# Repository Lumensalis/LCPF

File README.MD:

# Lumensalis CircuitPython Framework

This is a collection of CircuitPython code for use with TerrainTronics products sponsored by [Lumensalis Terrain](https://lumensalis.com)
 
 General project overview : https://lumensalis.com/Projects/LCPF

 - [Quick Start for the technically challenged...](docs/GettingStarted/QuickStart.mdx)
 
 - [Supported Controllers](docs/Controllers/SupportedControllers.mdx)
   - currently the ONLY tested controller is the [LolinS2Mini ESP32-S2](docs/Controllers/LolinS2Mini.mdx)
   - to setup a new LolinS2Mini, first do the [initial CircuitPython install](docs/Controllers/LolinS2Mini.mdx#initial-setup), then install the [dependencies](docs/CIRCUITPY_Dependncies.mdx)

 - [Getting Started](docs/GettingStarted/GettingStarted.mdx)
 - [Repo Contents](docs/RepoContents.mdx)

 - [source subrepo](https://github.com/Lumensalis/LCPF) 
  - most actual source code is in https://github.com/Lumensalis/LCPF
  - this repo holds most of the documentation, mechanisms for
    managing CircuitPython dependencies, and other bits related
    to the project _other_ than the framework code

# License
 
This is NOT an Open Source project.  The _only_ thing the license permits you
to use this for is your own personal projects.  You can _NOT_ share this
software _OR ANYTHING YOU BUILD USING IT_ with anyone else under
this license.

I will _probably_ change to a less restrictive license at some point, although 
it will probably _NOT_ allow any form of commercial use, especially selling 
any physical products including this software pre-installed.  I'd
prefer changing to an Open Source(ish) license, _if_ I can find one that
allows me to keep things free and easy _only_ for personal use.

If there is interest, I'll provide additional commercial license options.  

I'm also open to releasing this under a completely Open Source license in 
exchange for ongoing support of the project, although there would be a
 _substantial_ initial cost.  This may only be three months of effort so 
 far, but it's based on close to three decades of experience.

Actual license is in [License.txt](LICENSE.txt).

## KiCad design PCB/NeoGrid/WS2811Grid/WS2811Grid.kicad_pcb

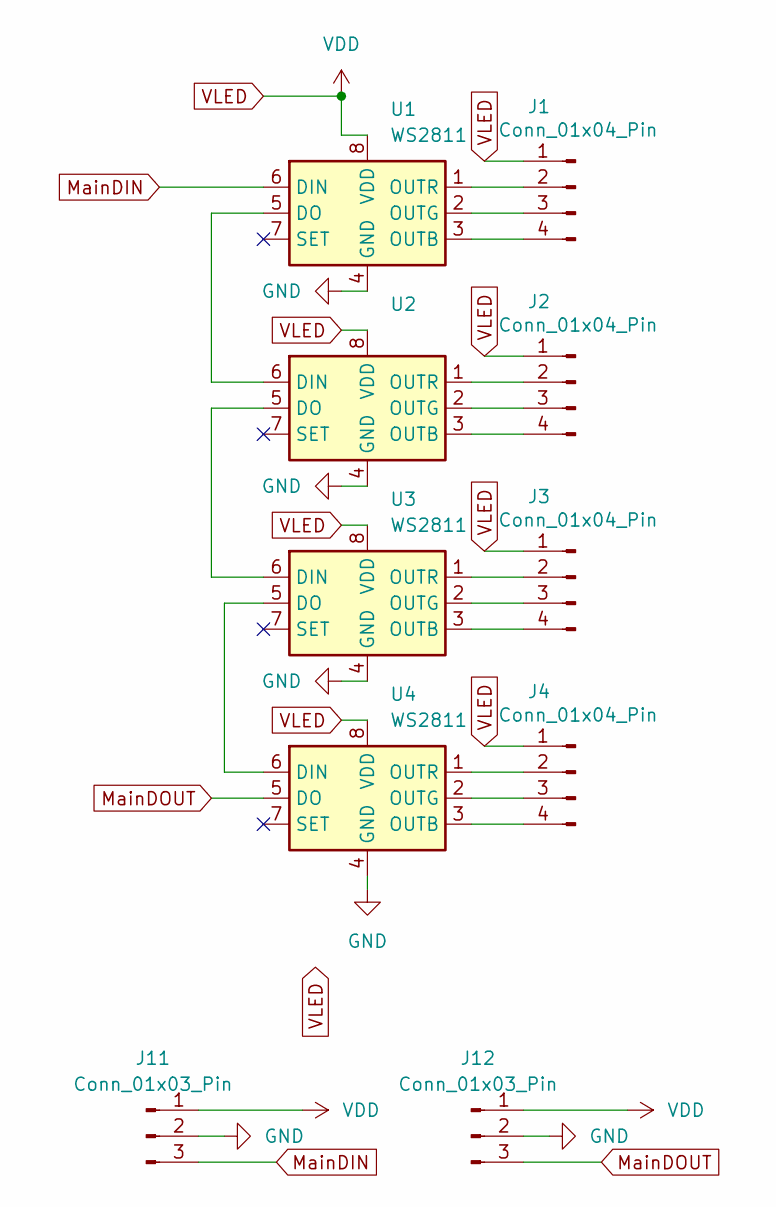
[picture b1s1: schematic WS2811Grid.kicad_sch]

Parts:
J1, J2, J3, J4: Conn_01x04_Pin; PinHeader_1x04_P2.54mm_Vertical
J11, J12: Conn_01x03_Pin; PinHeader_1x03_P2.54mm_Vertical
U1, U2, U3, U4: WS2811; SOIC-8_3.9x4.9mm_P1.27mm

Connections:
GND: J11.2, J12.2, U1.4 (GND), U2.4 (GND), U3.4 (GND), U4.4 (GND)
MainDIN: J11.3, U1.6 (DIN)
MainDOUT: J12.3, U4.5 (DO)
unnamed: J1.2, U1.1 (OUTR)
unnamed: J1.3, U1.2 (OUTG)
unnamed: J1.4, U1.3 (OUTB)
unnamed: J2.2, U2.1 (OUTR)
unnamed: J2.3, U2.2 (OUTG)
unnamed: J2.4, U2.3 (OUTB)
unnamed: J3.2, U3.1 (OUTR)
unnamed: J3.3, U3.2 (OUTG)
unnamed: J3.4, U3.3 (OUTB)
unnamed: J4.2, U4.1 (OUTR)
unnamed: J4.3, U4.2 (OUTG)
unnamed: J4.4, U4.3 (OUTB)
unnamed: U1.5 (DO), U2.6 (DIN)
unnamed: U2.5 (DO), U3.6 (DIN)
unnamed: U3.5 (DO), U4.6 (DIN)
VLED: J1.1, J2.1, J3.1, J4.1, J11.1, J12.1, U1.8 (VDD), U2.8 (VDD), U3.8 (VDD), U4.8 (VDD)

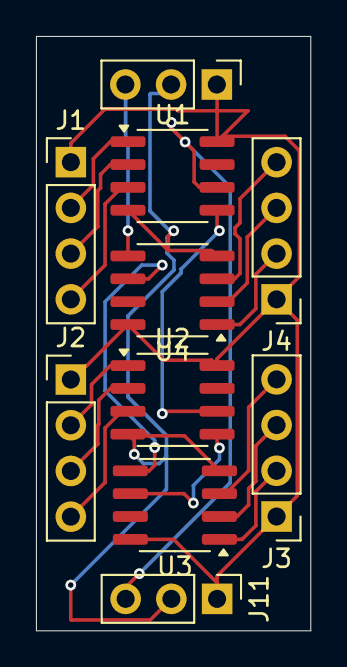
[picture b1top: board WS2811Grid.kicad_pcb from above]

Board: 2 copper layers, 15.2 x 33.0 mm, 10 parts (0 on the bottom side), 19 nets.

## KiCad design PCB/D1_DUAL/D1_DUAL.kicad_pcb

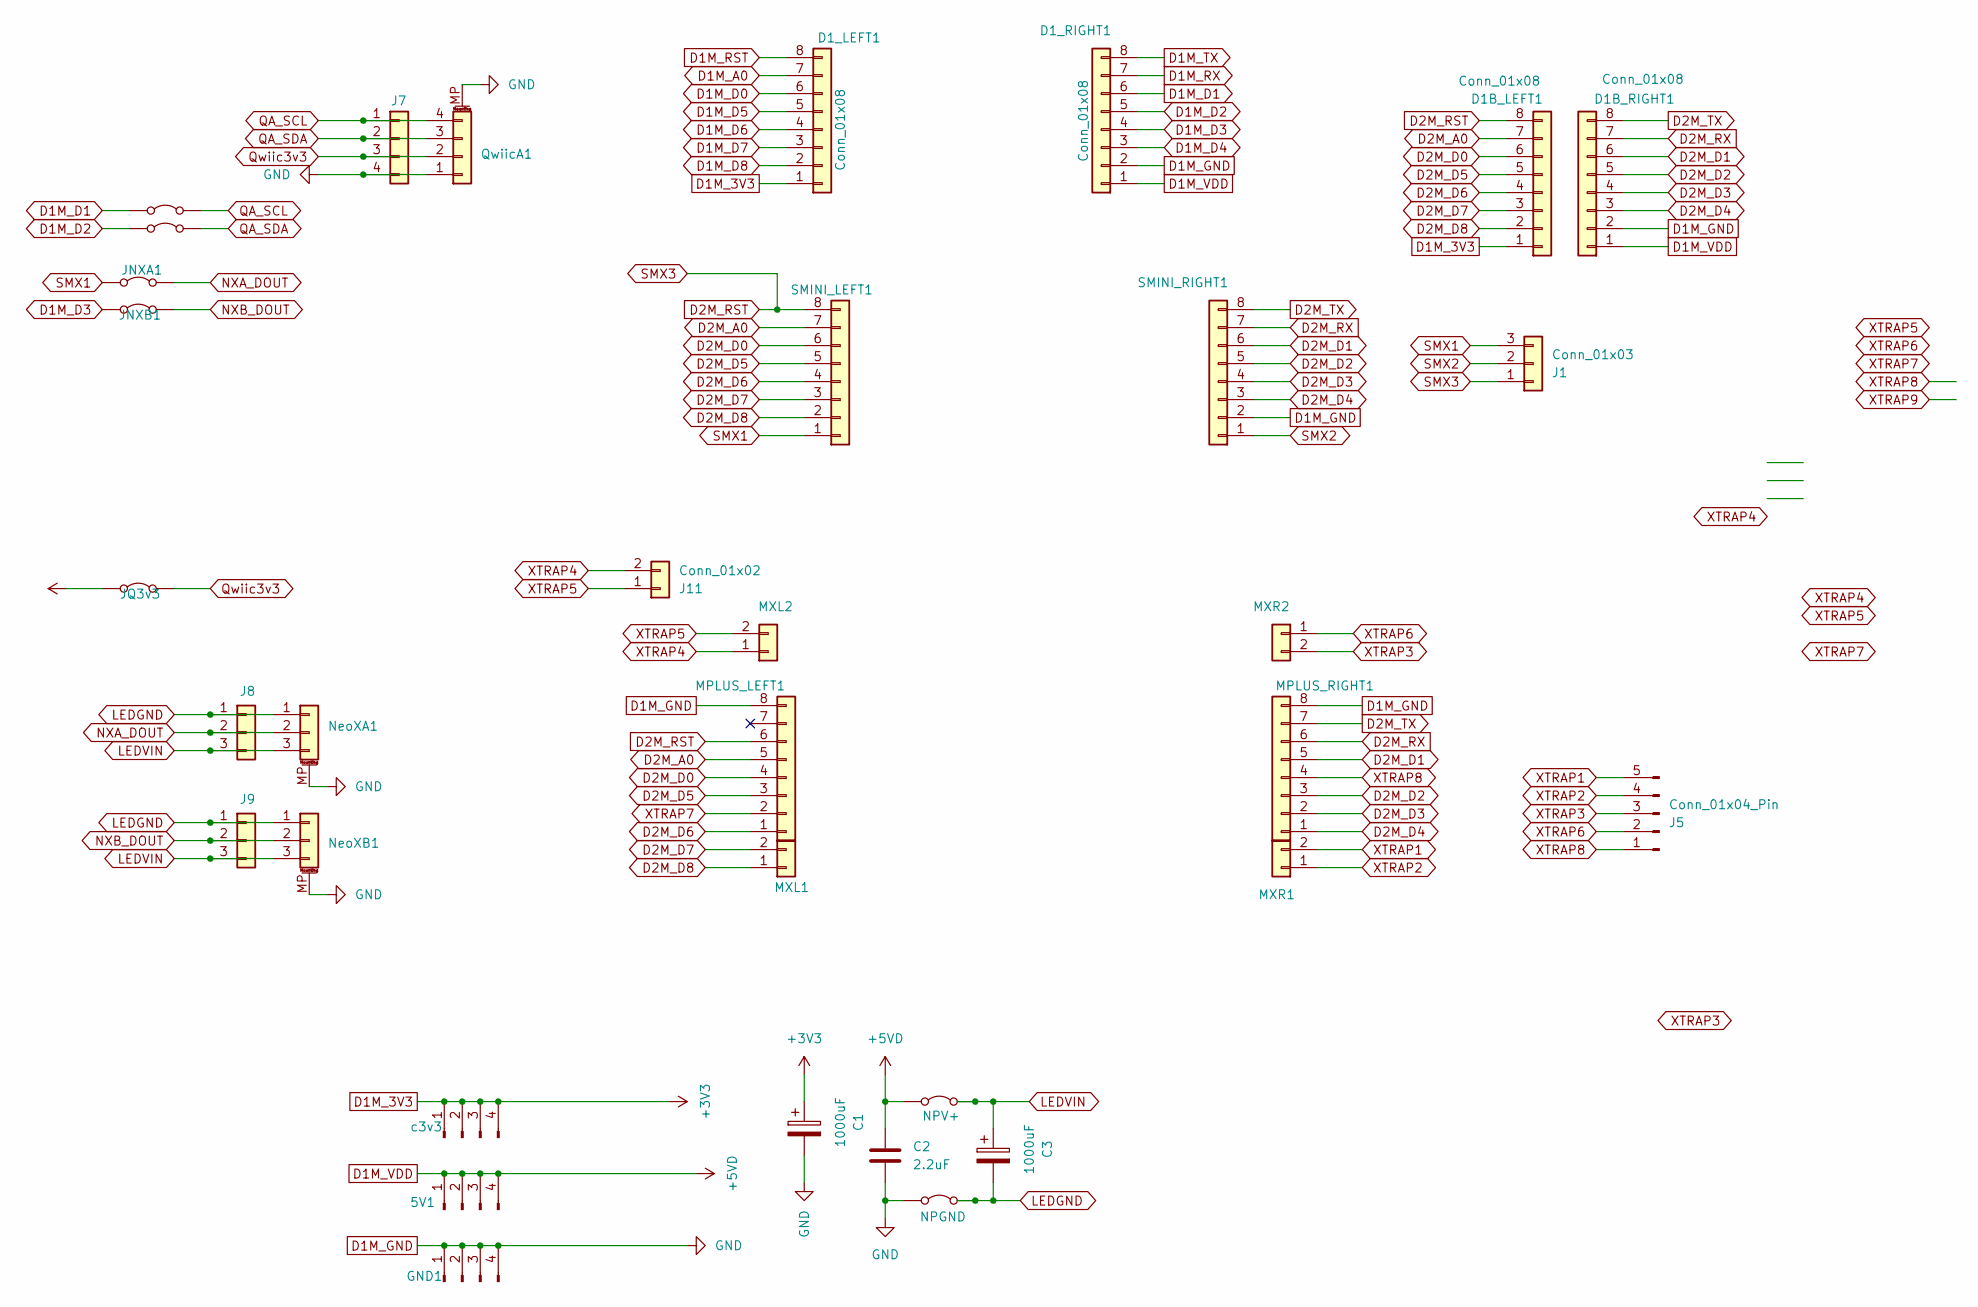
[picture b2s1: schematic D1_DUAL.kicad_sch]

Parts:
5V1: Conn_01x04_Pin; PinHeader_1x04_P2.54mm_Vertical
C1, C3: 1000uF; CP_Radial_D4.0mm_P1.50mm
C2: 2.2uF; C_Disc_D3.0mm_W2.0mm_P2.50mm
D1B_LEFT1, D1B_RIGHT1, D1_LEFT1, D1_RIGHT1: Conn_01x08; PinSocket_1x08_P2.54mm_Vertical
GND1: Conn_01x04_Pin; PinHeader_1x04_P2.54mm_Vertical
J1: Conn_01x03; PinHeader_1x03_P2.54mm_Horizontal
J5: Conn_01x04_Pin; PinHeader_1x05_P2.54mm_Horizontal
J7: Conn_01x04; PinHeader_1x04_P2.54mm_Vertical
J8, J9: Conn_01x03; PinHeader_1x03_P2.54mm_Vertical
J11: Conn_01x02; PinHeader_1x02_P2.54mm_Horizontal
JLGND1: NPGND; PinHeader_1x02_P2.54mm_Vertical
JLVDD1: NPV+; PinHeader_1x02_P2.54mm_Vertical
JNXA1: SolderJumper_2_Bridged; SolderJumper-2_P1.3mm_Bridged_RoundedPad1.0x1.5mm
JNXB1: SolderJumper_2_Bridged; SolderJumper-2_P1.3mm_Bridged_RoundedPad1.0x1.5mm
JQ3v3: SolderJumper_2_Bridged; SolderJumper-2_P1.3mm_Bridged2Bar_RoundedPad1.0x1.5mm
MPLUS_LEFT1: Conn_01x8; PinSocket_1x08_P2.54mm_Vertical
MPLUS_RIGHT1: Conn_01x8; PinSocket_1x08_P2.54mm_Vertical
MXL1, MXL2: Conn_01x02; PinSocket_1x02_P2.54mm_Vertical
MXR1, MXR2: Conn_01x02; PinSocket_1x02_P2.54mm_Vertical
NeoXA1: Conn_01x03_MountingPin; JST_GH_SM03B-GHS-TB_1x03-1MP_P1.25mm_Horizontal
NeoXB1: Conn_01x03_MountingPin; JST_GH_SM03B-GHS-TB_1x03-1MP_P1.25mm_Horizontal
QwiicA1: Conn_01x04_MountingPin; JST_SH_SM04B-SRSS-TB_1x04-1MP_P1.00mm_Horizontal
SCL_A1: SolderJumper_2_Bridged; SolderJumper-2_P1.3mm_Bridged_RoundedPad1.0x1.5mm
SDA_A1: SolderJumper_2_Bridged; SolderJumper-2_P1.3mm_Bridged_RoundedPad1.0x1.5mm
SMINI_LEFT1: Conn_01x08; PinSocket_1x08_P2.54mm_Vertical
SMINI_RIGHT1: Conn_01x08; PinSocket_1x08_P2.54mm_Vertical
c3v3: Conn_01x04_Pin; PinHeader_1x02_P2.54mm_Vertical

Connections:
D1M_3V3: C1.1, D1B_LEFT1.1, D1_LEFT1.1, JQ3v3.1 (A), c3v3.1, c3v3.2, c3v3.3, c3v3.4
D1M_A0: D1_LEFT1.7
D1M_D0: D1_LEFT1.6
D1M_D1: D1_RIGHT1.6, SCL_A1.1 (A)
D1M_D2: D1_RIGHT1.5, SDA_A1.1 (A)
D1M_D3: D1_RIGHT1.4, JNXB1.1 (A)
D1M_D4: D1_RIGHT1.3
D1M_D5: D1_LEFT1.5
D1M_D6: D1_LEFT1.4
D1M_D7: D1_LEFT1.3
D1M_D8: D1_LEFT1.2
D1M_GND: C1.2, C2.2, D1B_RIGHT1.2, D1_RIGHT1.2, GND1.1, GND1.2, GND1.3, GND1.4, J7.4, JLGND1.1 (A), MPLUS_LEFT1.8, MPLUS_RIGHT1.8, NeoXA1.MP (MountPin), NeoXB1.MP (MountPin), QwiicA1.1, QwiicA1.MP (MountPin), SMINI_RIGHT1.2
D1M_RST: D1_LEFT1.8
D1M_RX: D1_RIGHT1.7
D1M_TX: D1_RIGHT1.8
D1M_VDD: 5V1.1, 5V1.2, 5V1.3, 5V1.4, C2.1, D1B_RIGHT1.1, D1_RIGHT1.1, JLVDD1.1 (A)
D2M_A0: D1B_LEFT1.7, MPLUS_LEFT1.5, SMINI_LEFT1.7
D2M_D0: D1B_LEFT1.6, MPLUS_LEFT1.4, SMINI_LEFT1.6
D2M_D1: D1B_RIGHT1.6, MPLUS_RIGHT1.5, SMINI_RIGHT1.6
D2M_D2: D1B_RIGHT1.5, MPLUS_RIGHT1.3, SMINI_RIGHT1.5
D2M_D3: D1B_RIGHT1.4, MPLUS_RIGHT1.2, SMINI_RIGHT1.4
D2M_D4: D1B_RIGHT1.3, MPLUS_RIGHT1.1, SMINI_RIGHT1.3
D2M_D5: D1B_LEFT1.5, MPLUS_LEFT1.3, SMINI_LEFT1.5
D2M_D6: D1B_LEFT1.4, MPLUS_LEFT1.1, SMINI_LEFT1.4
D2M_D7: D1B_LEFT1.3, MXL1.2, SMINI_LEFT1.3
D2M_D8: D1B_LEFT1.2, MXL1.1, SMINI_LEFT1.2
D2M_RST: D1B_LEFT1.8, J1.1, MPLUS_LEFT1.6, SMINI_LEFT1.8
D2M_RX: D1B_RIGHT1.7, MPLUS_RIGHT1.6, SMINI_RIGHT1.7
D2M_TX: D1B_RIGHT1.8, MPLUS_RIGHT1.7, SMINI_RIGHT1.8
LEDGND: C3.2, J8.1, J9.1, JLGND1.2 (B), NeoXA1.1, NeoXB1.1
LEDVIN: C3.1, J8.3, J9.3, JLVDD1.2 (B), NeoXA1.3, NeoXB1.3
NXA_DOUT: J8.2, JNXA1.2 (B), NeoXA1.2
NXB_DOUT: J9.2, JNXB1.2 (B), NeoXB1.2
QA_SCL: J7.1, QwiicA1.4, SCL_A1.2 (B)
QA_SDA: J7.2, QwiicA1.3, SDA_A1.2 (B)
Qwiic3v3: J7.3, JQ3v3.2 (B), QwiicA1.2
SMX1: J1.3, JNXA1.1 (A), SMINI_LEFT1.1
SMX2: J1.2, SMINI_RIGHT1.1
XTRAP1: J5.5, MXR1.2
XTRAP2: J5.4, MXR1.1
XTRAP3: J5.3, MXR2.2
XTRAP4: J11.2, MXL2.1
XTRAP5: J11.1, MXL2.2
XTRAP6: J5.2, MXR2.1
XTRAP7: MPLUS_LEFT1.2
XTRAP8: J5.1, MPLUS_RIGHT1.4

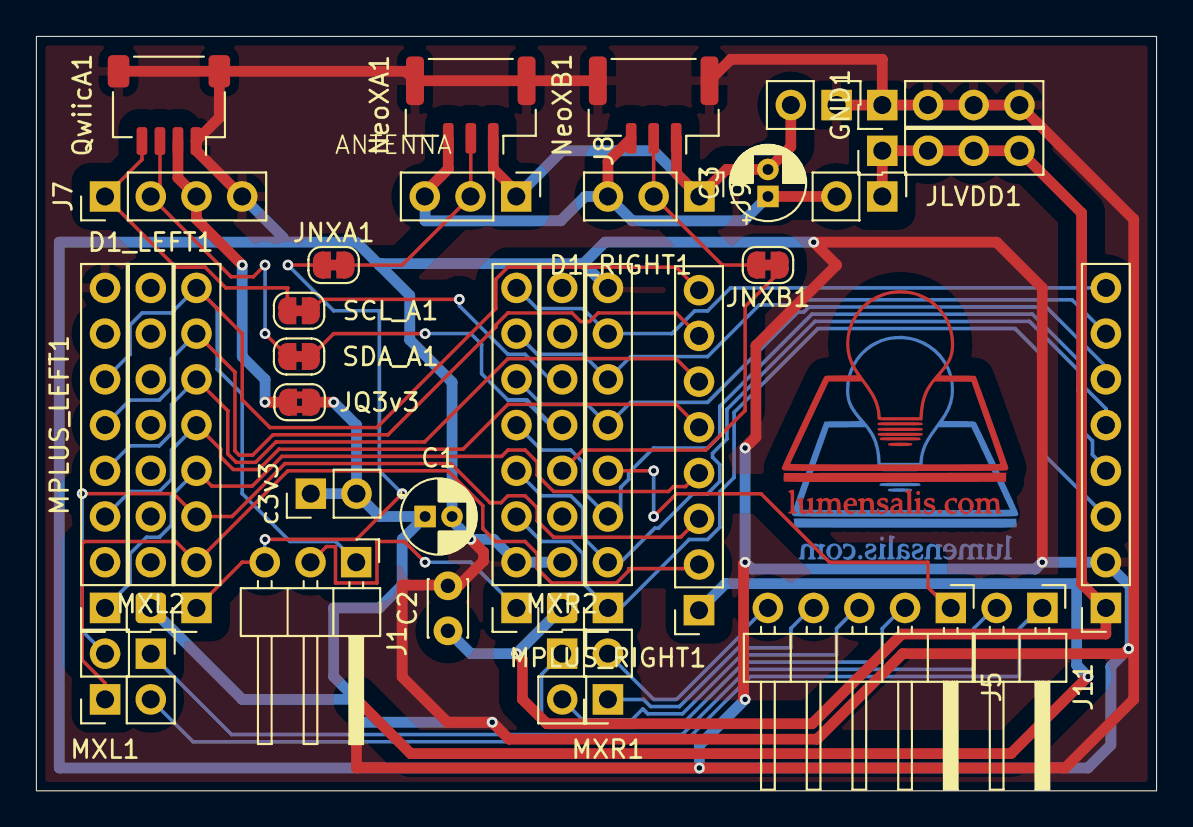
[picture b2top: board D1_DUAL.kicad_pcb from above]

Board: 2 copper layers, 62.2 x 41.9 mm, 34 parts (0 on the bottom side), 35 nets.

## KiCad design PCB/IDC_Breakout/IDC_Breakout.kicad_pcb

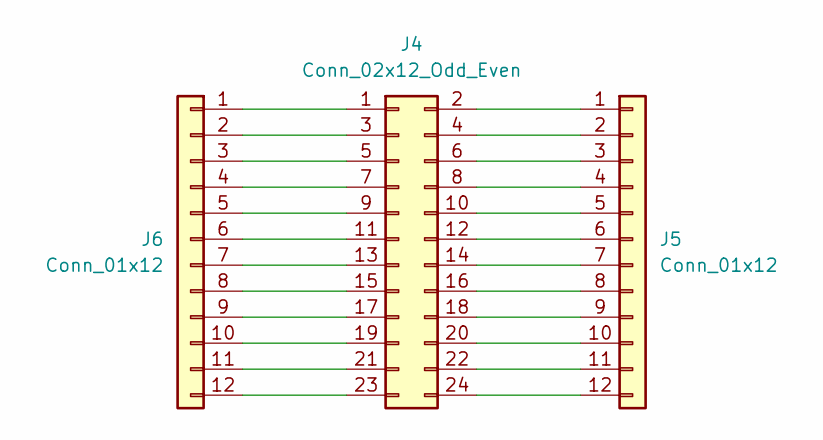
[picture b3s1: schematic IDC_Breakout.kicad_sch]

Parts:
J4: Conn_02x12_Odd_Even; PinSocket_2x12_P2.54mm_Vertical
J5, J6: Conn_01x12; PinHeader_1x12_P2.54mm_Vertical

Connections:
unnamed: J4.1, J6.1
unnamed: J4.2, J5.1
unnamed: J4.3, J6.2
unnamed: J4.4, J5.2
unnamed: J4.5, J6.3
unnamed: J4.6, J5.3
unnamed: J4.7, J6.4
unnamed: J4.8, J5.4
unnamed: J4.9, J6.5
unnamed: J4.10, J5.5
unnamed: J4.11, J6.6
unnamed: J4.12, J5.6
unnamed: J4.13, J6.7
unnamed: J4.14, J5.7
unnamed: J4.15, J6.8
unnamed: J4.16, J5.8
unnamed: J4.17, J6.9
unnamed: J4.18, J5.9
unnamed: J4.19, J6.10
unnamed: J4.20, J5.10
unnamed: J4.21, J6.11
unnamed: J4.22, J5.11
unnamed: J4.23, J6.12
unnamed: J4.24, J5.12

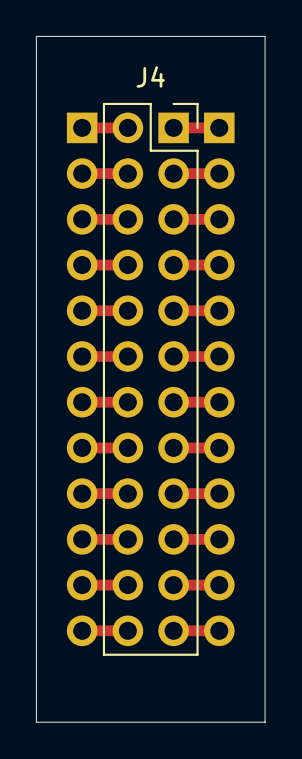
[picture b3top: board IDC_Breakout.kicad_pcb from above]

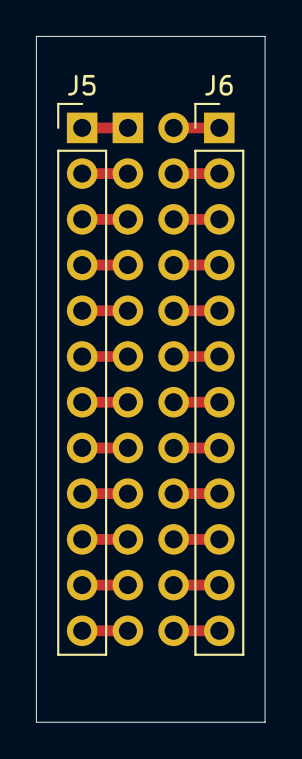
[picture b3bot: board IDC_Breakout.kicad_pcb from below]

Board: 2 copper layers, 12.7 x 38.1 mm, 3 parts (2 on the bottom side), 24 nets.

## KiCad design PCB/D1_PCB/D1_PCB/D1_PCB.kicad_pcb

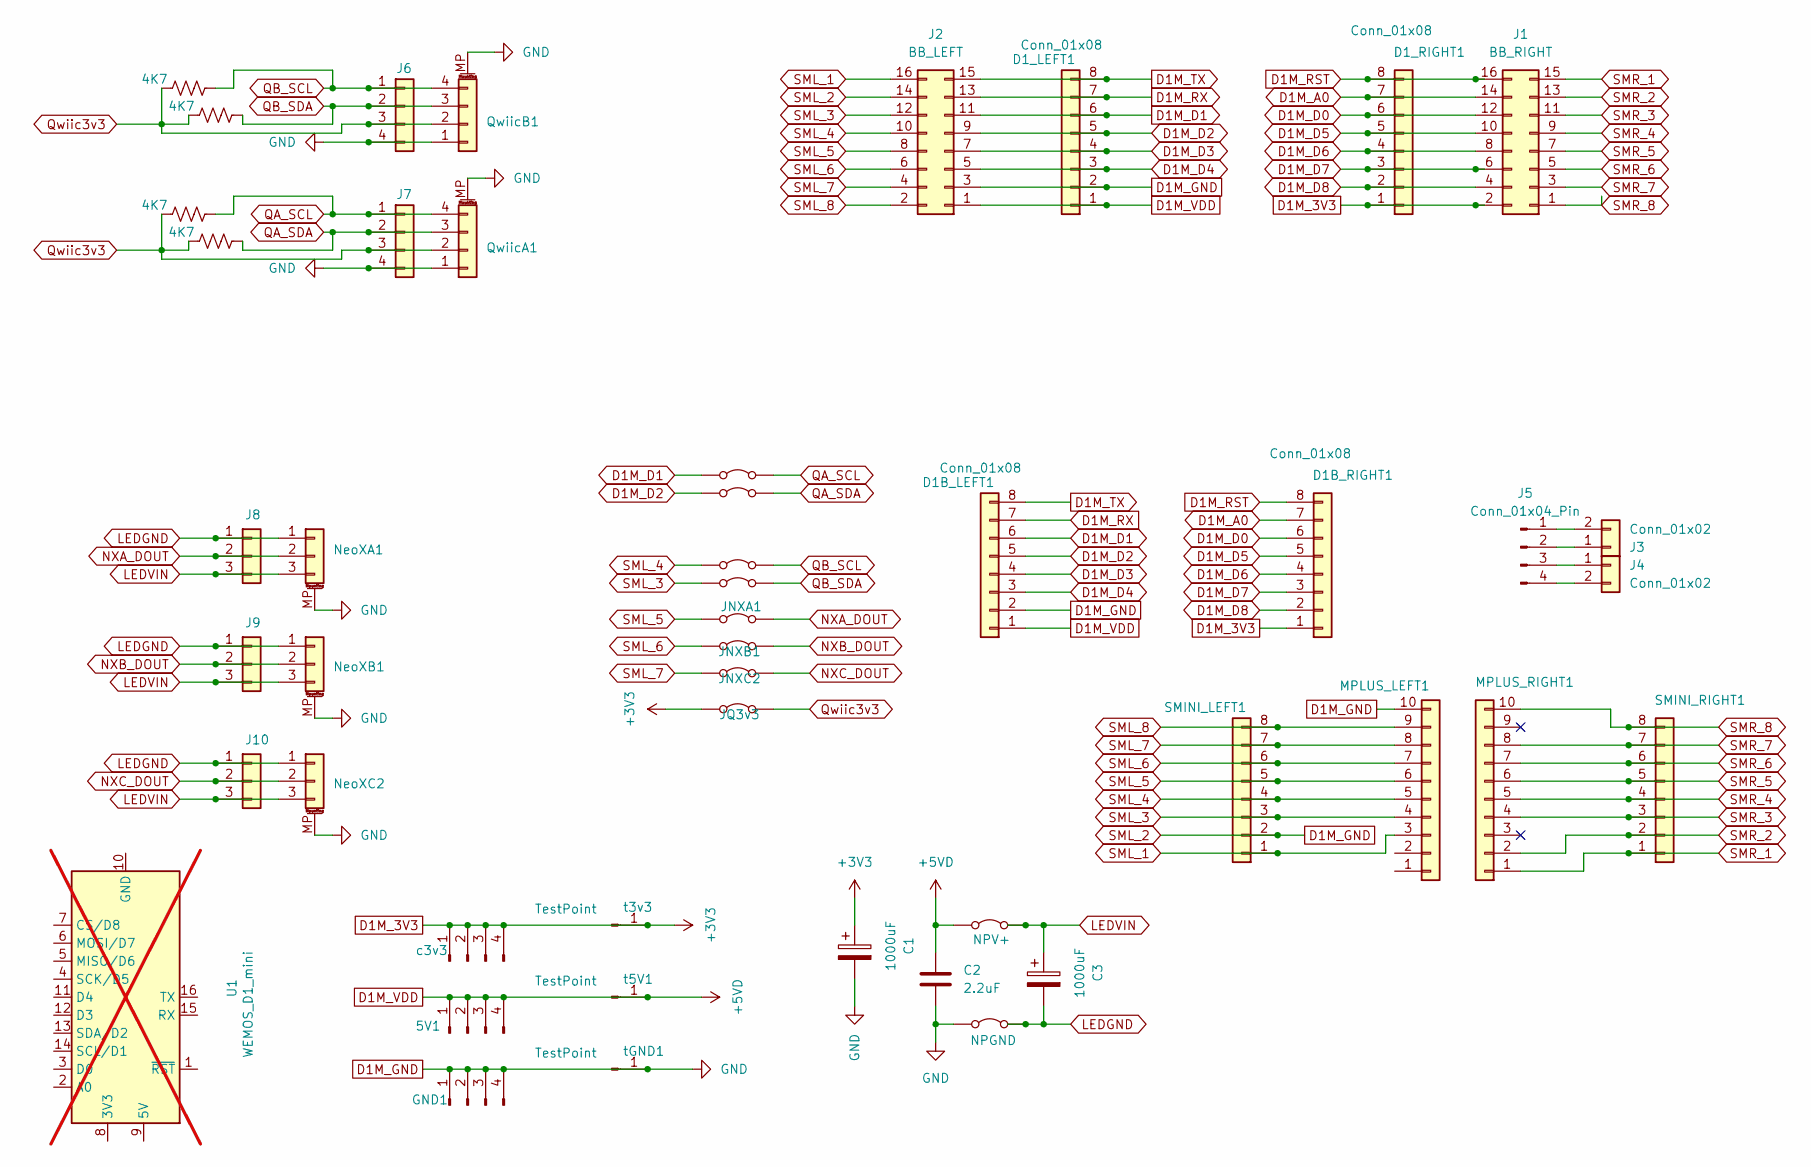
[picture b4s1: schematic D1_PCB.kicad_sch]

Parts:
5V1: Conn_01x04_Pin; PinHeader_1x04_P2.54mm_Vertical
C1, C3: 1000uF; CP_Radial_D4.0mm_P1.50mm
C2: 2.2uF; C_Disc_D3.0mm_W2.0mm_P2.50mm
D1B_LEFT1, D1B_RIGHT1, D1_LEFT1, D1_RIGHT1: Conn_01x08; PinSocket_1x08_P2.54mm_Vertical
GND1: Conn_01x04_Pin; PinHeader_1x04_P2.54mm_Vertical
J1: BB_RIGHT; IDC-Header_2x08_P2.54mm_Vertical
J2: BB_LEFT; IDC-Header_2x08_P2.54mm_Vertical
J3, J4: Conn_01x02; PinSocket_1x02_P2.54mm_Vertical
J5: Conn_01x04_Pin; PinHeader_1x04_P2.54mm_Vertical
J6, J7: Conn_01x04; PinHeader_1x04_P2.54mm_Vertical
J8, J9, J10: Conn_01x03; PinHeader_1x03_P2.54mm_Vertical
JLGND1: NPGND; PinHeader_1x02_P2.54mm_Vertical
JLVDD1: NPV+; PinHeader_1x02_P2.54mm_Vertical
JNXA1: SolderJumper_2_Bridged; PinHeader_1x02_P2.54mm_Vertical
JNXB1: SolderJumper_2_Bridged; PinHeader_1x02_P2.54mm_Vertical
JNXC2: SolderJumper_2_Bridged; PinHeader_1x02_P2.54mm_Vertical
JQ3v3: SolderJumper_2_Bridged; PinHeader_1x02_P2.54mm_Vertical
MPLUS_LEFT1: Conn_01x10; PinSocket_1x10_P2.54mm_Vertical
MPLUS_RIGHT1: Conn_01x10; PinSocket_1x10_P2.54mm_Vertical
NeoXA1: Conn_01x03_MountingPin; JST_GH_SM03B-GHS-TB_1x03-1MP_P1.25mm_Horizontal
NeoXB1: Conn_01x03_MountingPin; JST_GH_SM03B-GHS-TB_1x03-1MP_P1.25mm_Horizontal
NeoXC2: Conn_01x03_MountingPin; JST_GH_SM03B-GHS-TB_1x03-1MP_P1.25mm_Horizontal
QwiicA1: Conn_01x04_MountingPin; JST_SH_SM04B-SRSS-TB_1x04-1MP_P1.00mm_Horizontal
QwiicB1: Conn_01x04_MountingPin; JST_SH_SM04B-SRSS-TB_1x04-1MP_P1.00mm_Horizontal
R1, R2, R3, R4: 4K7; R_Axial_DIN0204_L3.6mm_D1.6mm_P2.54mm_Vertical
SCL_A1: SolderJumper_2_Bridged; PinHeader_1x02_P2.54mm_Vertical
SCL_B1: SolderJumper_2_Bridged; PinHeader_1x02_P2.54mm_Vertical
SDA_A1: SolderJumper_2_Bridged; PinHeader_1x02_P2.54mm_Vertical
SDA_B1: SolderJumper_2_Bridged; PinHeader_1x02_P2.54mm_Vertical
SMINI_LEFT1: Conn_01x08; PinSocket_1x08_P2.54mm_Vertical
SMINI_RIGHT1: Conn_01x08; PinSocket_1x08_P2.54mm_Vertical
U1: WEMOS_D1_mini; WEMOS_D1_mini_light; not fitted
c3v3: Conn_01x04_Pin; PinHeader_1x04_P2.54mm_Vertical
t3v3, t5V1: TestPoint; PinHeader_1x01_P2.54mm_Vertical
tGND1: TestPoint; PinHeader_1x01_P2.54mm_Vertical

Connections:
D1M_3V3: C1.1, D1B_RIGHT1.1, D1_RIGHT1.1, J1.2, JQ3v3.1 (A), c3v3.1, c3v3.2, c3v3.3, c3v3.4, t3v3.1
D1M_A0: D1B_RIGHT1.7, D1_RIGHT1.7, J1.14
D1M_D0: D1B_RIGHT1.6, D1_RIGHT1.6, J1.12
D1M_D1: D1B_LEFT1.6, D1_LEFT1.6, J2.11, SCL_A1.1 (A)
D1M_D2: D1B_LEFT1.5, D1_LEFT1.5, J2.9, SDA_A1.1 (A)
D1M_D3: D1B_LEFT1.4, D1_LEFT1.4, J2.7
D1M_D4: D1B_LEFT1.3, D1_LEFT1.3, J2.5
D1M_D5: D1B_RIGHT1.5, D1_RIGHT1.5, J1.10
D1M_D6: D1B_RIGHT1.4, D1_RIGHT1.4, J1.8
D1M_D7: D1B_RIGHT1.3, D1_RIGHT1.3, J1.6
D1M_D8: D1B_RIGHT1.2, D1_RIGHT1.2, J1.4
D1M_GND: C1.2, C2.2, D1B_LEFT1.2, D1_LEFT1.2, GND1.1, GND1.2, GND1.3, GND1.4, J2.3, J2.14, J6.4, J7.4, JLGND1.1 (A), MPLUS_LEFT1.10, NeoXA1.MP (MountPin), NeoXB1.MP (MountPin), NeoXC2.MP (MountPin), QwiicA1.1, QwiicA1.MP (MountPin), QwiicB1.1, QwiicB1.MP (MountPin), SMINI_LEFT1.2, tGND1.1
D1M_RST: D1B_RIGHT1.8, D1_RIGHT1.8, J1.16
D1M_RX: D1B_LEFT1.7, D1_LEFT1.7, J2.13
D1M_TX: D1B_LEFT1.8, D1_LEFT1.8, J2.15
D1M_VDD: 5V1.1, 5V1.2, 5V1.3, 5V1.4, C2.1, D1B_LEFT1.1, D1_LEFT1.1, J2.1, JLVDD1.1 (A), t5V1.1
LEDGND: C3.2, J8.1, J9.1, J10.1, JLGND1.2 (B), NeoXA1.1, NeoXB1.1, NeoXC2.1
LEDVIN: C3.1, J8.3, J9.3, J10.3, JLVDD1.2 (B), NeoXA1.3, NeoXB1.3, NeoXC2.3
NXA_DOUT: J8.2, JNXA1.2 (B), NeoXA1.2
NXB_DOUT: J9.2, JNXB1.2 (B), NeoXB1.2
NXC_DOUT: J10.2, JNXC2.2 (B), NeoXC2.2
unnamed: J3.1, J5.2
unnamed: J3.2, J5.1
unnamed: J4.1, J5.3
unnamed: J4.2, J5.4
QA_SCL: J7.1, QwiicA1.4, R3.2, SCL_A1.2 (B)
QA_SDA: J7.2, QwiicA1.3, R4.2, SDA_A1.2 (B)
QB_SCL: J6.1, QwiicB1.4, R2.2, SCL_B1.2 (B)
QB_SDA: J6.2, QwiicB1.3, R1.2, SDA_B1.2 (B)
Qwiic3v3: J6.3, J7.3, JQ3v3.2 (B), QwiicA1.2, QwiicB1.2, R1.1, R2.1, R3.1, R4.1
SML_1: J2.16, MPLUS_LEFT1.3, SMINI_LEFT1.1
SML_3: J2.12, MPLUS_LEFT1.4, SDA_B1.1 (A), SMINI_LEFT1.3
SML_4: J2.10, MPLUS_LEFT1.5, SCL_B1.1 (A), SMINI_LEFT1.4
SML_5: J2.8, JNXA1.1 (A), MPLUS_LEFT1.6, SMINI_LEFT1.5
SML_6: J2.6, JNXB1.1 (A), MPLUS_LEFT1.7, SMINI_LEFT1.6
SML_7: J2.4, JNXC2.1 (A), MPLUS_LEFT1.8, SMINI_LEFT1.7
SML_8: J2.2, MPLUS_LEFT1.9, SMINI_LEFT1.8
SMR_1: J1.15, MPLUS_RIGHT1.1, SMINI_RIGHT1.1
SMR_2: J1.13, MPLUS_RIGHT1.2, SMINI_RIGHT1.2
SMR_3: J1.11, MPLUS_RIGHT1.4, SMINI_RIGHT1.3
SMR_4: J1.9, MPLUS_RIGHT1.5, SMINI_RIGHT1.4
SMR_5: J1.7, MPLUS_RIGHT1.6, SMINI_RIGHT1.5
SMR_6: J1.5, MPLUS_RIGHT1.7, SMINI_RIGHT1.6
SMR_7: J1.3, MPLUS_RIGHT1.8, SMINI_RIGHT1.7
SMR_8: J1.1, MPLUS_RIGHT1.10, SMINI_RIGHT1.8

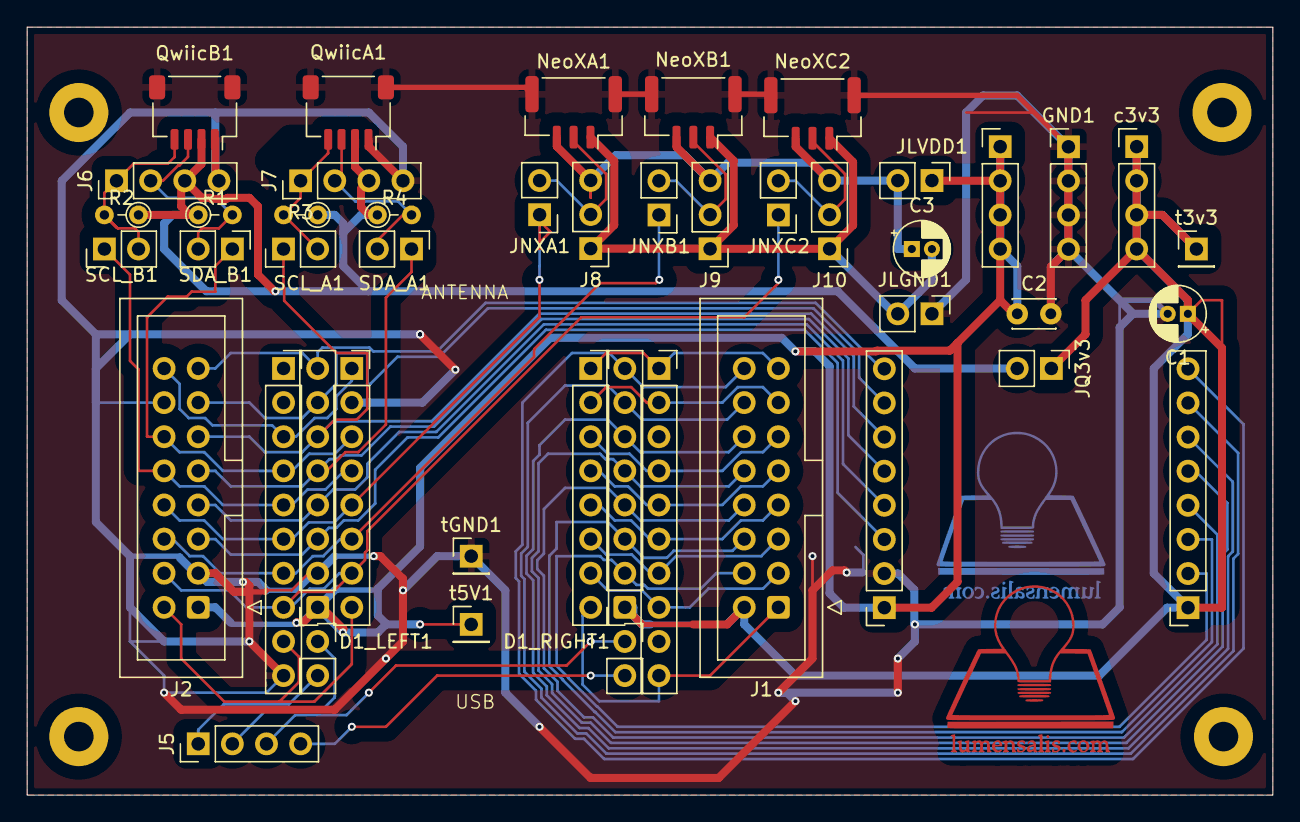
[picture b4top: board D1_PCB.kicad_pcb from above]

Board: 2 copper layers, 92.7 x 57.1 mm, 46 parts (0 on the bottom side), 45 nets.

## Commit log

2025-03-13 adding web server
2025-03-14 started adding demos
2025-03-14 lava timing
2025-03-14 initial SSD1306 display, RGB WebUI interaction, ...
2025-03-14 added memory stats, cleanup
2025-03-15 add TTCP_HOSTNAME / mdns support
2025-03-15 display cleanup
2025-03-15 Changes - file time hiccup?
2025-03-15 rename, relocate images
2025-03-15 more docs
2025-03-15 Move core to LumensalisCP module
2025-03-16 displayio support
2025-03-16 starting EZDisplay
2025-03-16 doc updates
2025-03-16 display / debug out tweaks
2025-03-16 more doc changes
2025-03-18 starting quick start docs
2025-03-18 more getting started
2025-03-18 D1 utility breadboard concept
2025-03-20 Utility D1 PCB changes
2025-03-23 Rules and Scenes
2025-03-30 lots of improvements
    - Timers & Triggers
    - Debuggable / dbgOut
    - more "typing" wrappers
    - "POD" type aliases in common ( TimeInSeconds,DegreesPerSecond,Degrees, ... )
    - ...
2025-03-30 Initial support for Audio
2025-03-30 support for more Qwiic/StemaQT & generic I2C devices
2025-03-30 IR remote and Servo moveTo
2025-03-30 initial Harlech Castle support
2025-03-30 demo/example updates (needs some cleanup...)
2025-03-30 PCB changes
2025-03-30 misc doc
2025-04-02 more sample format checking, mixer config
2025-04-02 initial normalization of api for Lights
2025-04-02 core buffs to MainManager, etc...
    - MainManager
    - callLater
    - addExitTask
    - addIntermediateVariable
    - audio / addI2SAudio
    - NamedLocalIdentifiable is now Debuggable
2025-04-02 TT Castle changes
    - move IR and Servo support from Caernarfon/Castle into LumensalisCP/Gadgets
    - asPin for normalizing pin argument handling
    - add keepAlive and global brightness (PWM OE) for Harlech
2025-04-02 dem OHZ mo betta
    - added useful bits so ```from TerrainTronics.Demos.DemoBase import *``` will get most/all of what a demo needs
    - added CaernarfonGate demo
    - added HarlechSimpleTest demo
2025-04-05 move framework code to lumensaliscplib sub module
2025-04-08 remove fss.log from git
2025-04-08 add CircuitPyDependencies
2025-04-08 changed origin / added bagend
2025-04-17 Working on Treasure Chest Demo
2025-04-18 initial DMX support
2025-06-05 notebook for close / buildwithus
2025-06-09 add PCA9685
2025-06-16 UV test design schematics
2025-06-18 add LICENSE.txt
2025-06-18 test support for mdx
2025-06-18 convert md to mdx
2025-06-18 createLCPFImage.sh
2025-06-19 move Nextra problem children to privateDocs
2025-06-19 remove docs - moving to submodule
2025-06-19 docs moved to LCPFDocs submodule
2025-06-22 ignore .VSCodeCounter
2025-06-22 fix lib paths for VSCode/Pylance/... analysis
2025-06-22 update sync drive / paths
2025-06-27 LCPF_CP_Install.zip
2025-06-27 more Sphinx/autodoc2 work
2025-07-05 update dependencies to cp10 bundle 250703
2025-07-12 add adafruit_connection_manager
2025-07-18 VCNL4040
2025-07-18 project catchup
2025-07-20 more pylance / typing cleanup
2025-07-20 more pylint
2025-07-21 ignore .pyi, handle new subdirs
2025-07-21 pylint / typings
2025-07-23 more pylint / typings
2025-07-23 enabled mpy-cross
2025-07-23 update submodules
2025-07-24 handle missing CIRCUITPY:\lib\ directory target
2025-08-02 cleaning up async
2025-08-03 async tracking
2025-08-03 CountedInstance
2025-08-04 NeoGrid PCB
2025-08-05 project settings
2025-08-05 submodules
2025-08-08 updating scripts for new .mpy dest dir
2025-08-08 sync submodules, remove install.zip
2025-08-13 notes on vscode-circuitpython build
2025-08-18 improve fake TypeVar
2025-08-21 Tunable tuning...
2025-08-22 trying PyCharm
2025-08-24 NamedLocalIdentifiable access
2025-08-24 LCPFProxy
